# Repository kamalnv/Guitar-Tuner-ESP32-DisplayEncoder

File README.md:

# ESP32 Guitar Tuner

A full-featured guitar tuner running on ESP32 with OLED display and rotary encoder for standard 6 string Guitar, 
has a Audio module for a mic, 

if you are looking for bass Guitar, 7 string guitar or as a Pedal you can try the V2 Branch

This code is by Emergent.sh use it at your descrete & risks.

## Hardware Requirements

### Components
1. **ESP32 DevKit** (or any generic ESP32 board)
2. **0.96" OLED Display Module with EC11 Rotary Encoder** 
   - Display: SSD1306, 128x32 pixels, I2C interface
   - Rotary Encoder: EC11 with push button
   - [Product Link](https://robu.in/product/0-96-inch-oled-display-screen-rotary-encoder/)
3. **Electret Microphone Module** (MAX9814 or MAX4466 recommended)

### Wiring Diagram

```
ESP32          OLED+Encoder Module (9-pin header)
------         ---------------------------------
3.3V    -----> VCC
GND     -----> GND
GPIO21  -----> SDA (I2C Data)
GPIO22  -----> SCL (I2C Clock)
GPIO32  -----> CLK (Encoder A)
GPIO33  -----> DT  (Encoder B)
GPIO25  -----> SW  (Encoder Button)

ESP32          Microphone Module
------         -----------------
3.3V    -----> VCC
GND     -----> GND
GPIO34  -----> OUT (Analog output)
```

### Pin Summary
| Function | ESP32 Pin |
|----------|-----------|
| I2C SDA  | GPIO 21   |
| I2C SCL  | GPIO 22   |
| Encoder CLK | GPIO 32 |
| Encoder DT  | GPIO 33 |
| Encoder SW  | GPIO 25 |
| Mic OUT  | GPIO 34   |

## Software Setup

### Arduino IDE Setup

1. **Install ESP32 Board Support**
   - Open Arduino IDE
   - Go to `File > Preferences`
   - Add to "Additional Board Manager URLs":
     ```
     https://raw.githubusercontent.com/espressif/arduino-esp32/gh-pages/package_esp32_index.json
     ```
   - Go to `Tools > Board > Boards Manager`
   - Search "ESP32" and install "esp32 by Espressif Systems"

2. **Install Required Libraries**
   - Go to `Sketch > Include Library > Manage Libraries`
   - Install:
     - `Adafruit GFX Library`
     - `Adafruit SSD1306`

3. **Select Board**
   - Go to `Tools > Board > ESP32 Arduino`
   - Select "ESP32 Dev Module" or your specific board

4. **Upload Settings**
   - Upload Speed: 921600
   - CPU Frequency: 240MHz
   - Flash Frequency: 80MHz
   - Flash Mode: QIO
   - Flash Size: 4MB
   - Partition Scheme: Default 4MB with spiffs

5. **Upload**
   - Connect ESP32 via USB
   - Select correct COM port in `Tools > Port`
   - Click Upload

## Usage

### Menu Navigation
- **Rotate encoder**: Switch between tuning modes
- **Push encoder**: Enter/exit tuning mode

### Tuning Modes

| Mode | Description | Strings |
|------|-------------|---------|
| **CHROMATIC** | All 12 notes | Any note |
| **STANDARD** | Standard guitar | E A D G B E |
| **DROP D** | Drop D guitar | D A D G B E |
| **HALF DOWN** | Half step down | Eb Ab Db Gb Bb Eb |
| **DROP C** | Drop C guitar | C G C F A D |
| **OPEN G** | Open G guitar | D G D G B D |
| **DADGAD** | Celtic tuning | D A D G A D |
| **7-STRING** | 7-string standard | B E A D G B E |
| **7STR DROP A** | 7-string Drop A | A E A D G B E |
| **BASS 4-STR** | 4-string bass | E A D G |
| **BASS 5-STR** | 5-string bass | B E A D G |
| **BASS DROP D** | Bass Drop D | D A D G |

### Display Information

#### Chromatic Mode
```
┌──────────────────────────┐
│ E4  329.6Hz         OK   │
│     +2.5c                │
│ ◄═══════════╪═══════════►│
└──────────────────────────┘
```
- Note name and octave
- Detected frequency
- Cents deviation (+/- from target)
- Visual tuning meter

#### Guitar Mode
```
┌──────────────────────────┐
│ STR 6: E2    82.4Hz      │
│ +3.2 cents     TUNE DN   │
│ ◄═══════════╪═══════════►│
└──────────────────────────┘
```
- String number and target note
- Detected frequency
- Cents deviation
- Tuning direction indicator
- Visual tuning meter

### Tuning Tips

1. **In Tune**: Meter indicator in center, "OK" or "IN TUNE!" displayed
2. **Tune Up**: Note is flat (low), increase string tension
3. **Tune Down**: Note is sharp (high), decrease string tension
4. **Target**: Keep cents deviation within ±5 cents

## Troubleshooting

### No Display
- Check I2C connections (SDA, SCL)
- Verify OLED address is 0x3C (can try 0x3D)
- Check power supply (3.3V)

### Encoder Not Responding
- Verify CLK, DT, SW connections
- Check for loose connections
- Ensure pull-up resistors are enabled (internal pull-ups used)

### No Pitch Detection
- Check microphone connections
- Ensure microphone gain is adequate
- Play note closer to microphone
- Check for environmental noise

### Inaccurate Readings
- Allow mic to warm up
- Play notes clearly and sustain
- Avoid background noise
- Ensure good power supply

## Technical Details

### Pitch Detection Algorithm
- Uses **autocorrelation** for fundamental frequency detection
- Sample rate: 8000 Hz
- Buffer size: 1024 samples
- Frequency range: 60 Hz - 1200 Hz (covers all guitar strings)

### Display
- Resolution: 128 x 32 pixels
- Driver: SSD1306
- Interface: I2C @ 400kHz

### Accuracy
- Typical accuracy: ±1-2 cents under good conditions
- Refresh rate: ~10 Hz

## License

Open source - free to use and modify.

## Credits

Built for the ESP32 platform using:
- Adafruit GFX Library
- Adafruit SSD1306 Library
- ESP32 Arduino Core

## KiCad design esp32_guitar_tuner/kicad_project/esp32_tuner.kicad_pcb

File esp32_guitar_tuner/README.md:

# ESP32 Guitar Tuner

A full-featured guitar tuner running on ESP32 with OLED display and rotary encoder.

## Hardware Requirements

### Components
1. **ESP32 DevKit** (or any generic ESP32 board)
2. **0.96" OLED Display Module with EC11 Rotary Encoder** 
   - Display: SSD1306, 128x32 pixels, I2C interface
   - Rotary Encoder: EC11 with push button
   - [Product Link](https://robu.in/product/0-96-inch-oled-display-screen-rotary-encoder/)
3. **Direct Guitar Input Circuit** (see below)

### Guitar Input Preamp Components
| Qty | Component | Value | Notes |
|-----|-----------|-------|-------|
| 1 | TL072 or LM358 | - | Dual op-amp IC |
| 1 | 1/4" Mono Audio Jack | - | Guitar input |
| 1 | Resistor | 1MΩ | Input impedance |
| 2 | Resistor | 100kΩ | Bias divider + feedback |
| 1 | Resistor | 10kΩ | Feedback |
| 1 | Resistor | 47kΩ | Output protection |
| 2 | Electrolytic Capacitor | 10µF | Coupling caps |
| 1 | Ceramic Capacitor | 100nF | Power decoupling |

### Wiring Diagram

```
ESP32          OLED+Encoder Module (9-pin header)
------         ---------------------------------
3.3V    -----> VCC
GND     -----> GND
GPIO21  -----> SDA (I2C Data)
GPIO22  -----> SCL (I2C Clock)
GPIO32  -----> CLK (Encoder A)
GPIO33  -----> DT  (Encoder B)
GPIO25  -----> SW  (Encoder Button)

ESP32          Guitar Preamp Circuit Output
------         ----------------------------
3.3V    -----> Op-amp VCC (pin 8)
GND     -----> Op-amp GND (pin 4)
GPIO34  -----> Preamp output (via 47kΩ)
```

### Guitar Input Preamp Schematic
```
                      +3.3V
                        │
                   ┌────┴────┐
                   │  100kΩ  │
                   └────┬────┘
                        │ (1.65V bias)
                   ┌────┴────┐
                   │  100kΩ  │
                   └────┬────┘
                        │
                       GND

  GUITAR    1MΩ     10µF    ┌─────────────┐
  TIP ────[====]───┤├──●────┤ 3   TL072  1├────┤├────[47kΩ]───> GPIO34
                        │    │      A      │   10µF
                   (bias)────┤ 2          8├────(+3.3V)
                             │             │
                         ┌───┤            4├────(GND)
                         │   └─────────────┘
                       10kΩ        │
                         │       100kΩ
                        GND        │
                                   └──────────────┘
                                   (feedback loop)

  GUITAR
  SLEEVE ──────────────────────────────────────────> GND
```

See `GUITAR_INPUT_CIRCUIT.h` for detailed schematic and breadboard layout.

### Pin Summary
| Function | ESP32 Pin |
|----------|-----------|
| I2C SDA  | GPIO 21   |
| I2C SCL  | GPIO 22   |
| Encoder CLK | GPIO 32 |
| Encoder DT  | GPIO 33 |
| Encoder SW  | GPIO 25 |
| Guitar IN | GPIO 34  |

## Software Setup

### Arduino IDE Setup

1. **Install ESP32 Board Support**
   - Open Arduino IDE
   - Go to `File > Preferences`
   - Add to "Additional Board Manager URLs":
     ```
     https://raw.githubusercontent.com/espressif/arduino-esp32/gh-pages/package_esp32_index.json
     ```
   - Go to `Tools > Board > Boards Manager`
   - Search "ESP32" and install "esp32 by Espressif Systems"

2. **Install Required Libraries**
   - Go to `Sketch > Include Library > Manage Libraries`
   - Install:
     - `Adafruit GFX Library`
     - `Adafruit SSD1306`

3. **Select Board**
   - Go to `Tools > Board > ESP32 Arduino`
   - Select "ESP32 Dev Module" or your specific board

4. **Upload Settings**
   - Upload Speed: 921600
   - CPU Frequency: 240MHz
   - Flash Frequency: 80MHz
   - Flash Mode: QIO
   - Flash Size: 4MB
   - Partition Scheme: Default 4MB with spiffs

5. **Upload**
   - Connect ESP32 via USB
   - Select correct COM port in `Tools > Port`
   - Click Upload

## Usage

### Menu Navigation
- **Rotate encoder**: Switch between tuning modes
- **Push encoder**: Enter/exit tuning mode

### Tuning Modes

| Mode | Description | Strings |
|------|-------------|---------|
| **CHROMATIC** | All 12 notes | Any note |
| **STANDARD** | Standard guitar | E A D G B E |
| **DROP D** | Drop D guitar | D A D G B E |
| **HALF DOWN** | Half step down | Eb Ab Db Gb Bb Eb |
| **DROP C** | Drop C guitar | C G C F A D |
| **OPEN G** | Open G guitar | D G D G B D |
| **DADGAD** | Celtic tuning | D A D G A D |
| **7-STRING** | 7-string standard | B E A D G B E |
| **7STR DROP A** | 7-string Drop A | A E A D G B E |
| **BASS 4-STR** | 4-string bass | E A D G |
| **BASS 5-STR** | 5-string bass | B E A D G |
| **BASS DROP D** | Bass Drop D | D A D G |

### Display Information

#### Chromatic Mode
```
┌──────────────────────────┐
│ E4  329.6Hz         OK   │
│     +2.5c                │
│ ◄═══════════╪═══════════►│
└──────────────────────────┘
```
- Note name and octave
- Detected frequency
- Cents deviation (+/- from target)
- Visual tuning meter

#### Guitar Mode
```
┌──────────────────────────┐
│ STR 6: E2    82.4Hz      │
│ +3.2 cents     TUNE DN   │
│ ◄═══════════╪═══════════►│
└──────────────────────────┘
```
- String number and target note
- Detected frequency
- Cents deviation
- Tuning direction indicator
- Visual tuning meter

### Tuning Tips

1. **In Tune**: Meter indicator in center, "OK" or "IN TUNE!" displayed
2. **Tune Up**: Note is flat (low), increase string tension
3. **Tune Down**: Note is sharp (high), decrease string tension
4. **Target**: Keep cents deviation within ±5 cents

## Troubleshooting

### No Display
- Check I2C connections (SDA, SCL)
- Verify OLED address is 0x3C (can try 0x3D)
- Check power supply (3.3V)

### Encoder Not Responding
- Verify CLK, DT, SW connections
- Check for loose connections
- Ensure pull-up resistors are enabled (internal pull-ups used)

### No Pitch Detection
- Check guitar cable connection
- Verify preamp circuit is powered (3.3V to op-amp)
- Check 10µF capacitors are correct polarity
- Ensure op-amp output reaches GPIO34
- Try a different guitar/cable

### Inaccurate Readings
- Adjust preamp gain if signal clips (reduce 100kΩ feedback resistor)
- Check for loose connections in preamp circuit
- Ensure good solder joints
- Use shielded cable from preamp to ESP32

### Signal Too Weak
- Increase gain: use 220kΩ instead of 100kΩ for feedback
- Check guitar volume knob is up
- Verify 1MΩ input resistor value

### Signal Clipping (Distorted)
- Decrease gain: use 47kΩ instead of 100kΩ for feedback
- For hot humbuckers, gain of 5-6 may be sufficient

## Technical Details

### Pitch Detection Algorithm
- Uses **autocorrelation** for fundamental frequency detection
- Sample rate: 8000 Hz
- Buffer size: 1024 samples
- Frequency range: 60 Hz - 1200 Hz (covers all guitar strings)

### Display
- Resolution: 128 x 32 pixels
- Driver: SSD1306
- Interface: I2C @ 400kHz

### Accuracy
- Typical accuracy: ±1-2 cents under good conditions
- Refresh rate: ~10 Hz

## License

Open source - free to use and modify.

## Credits

Built for the ESP32 platform using:
- Adafruit GFX Library
- Adafruit SSD1306 Library
- ESP32 Arduino Core

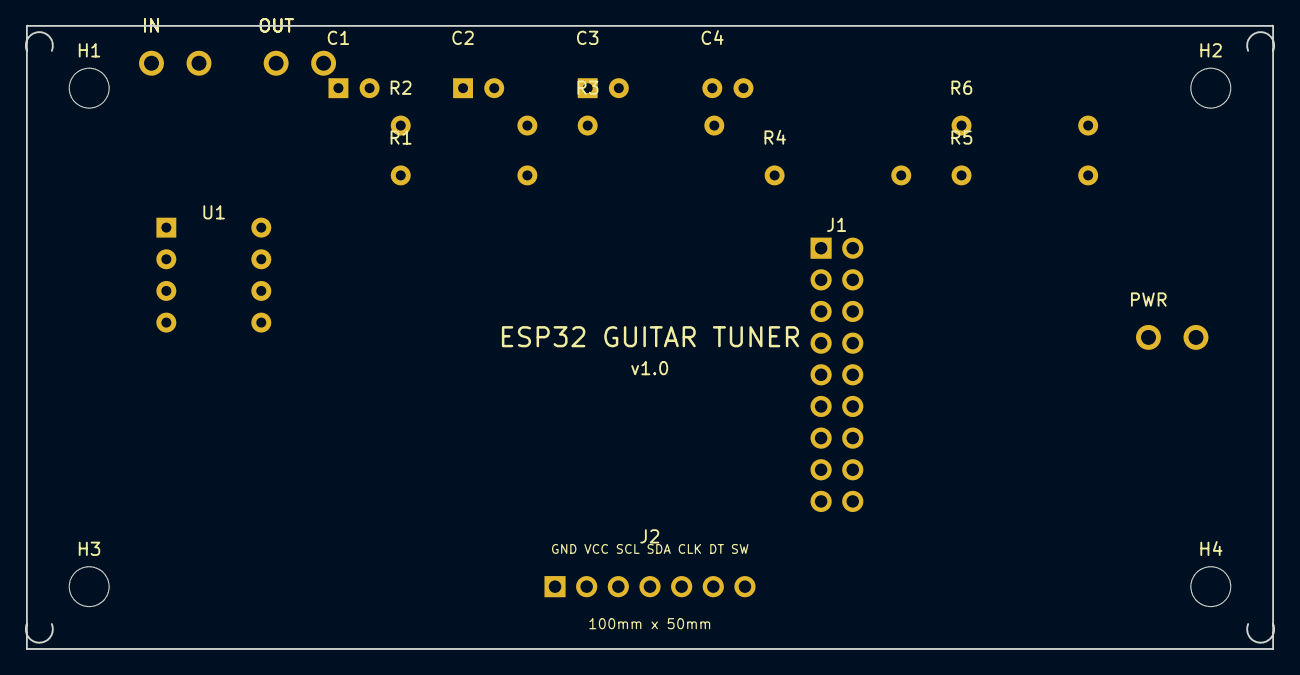
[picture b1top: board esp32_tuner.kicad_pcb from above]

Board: 2 copper layers, 100.2 x 50.0 mm, 20 parts (0 on the bottom side), 11 nets, no tracks yet.

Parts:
C1, C2, C3: 10uF; CP_Radial_D5.0mm_P2.50mm
C4: 100nF; C_Disc_D5.0mm_W2.5mm_P2.50mm
H1, H2, H3, H4: MountingHole_3.2mm_M3
IN: INPUT; SolderWirePad_1x02_P3.81mm_D1.0mm
J1: ESP-WROOM-32; PinHeader_2x09_P2.54mm_Vertical
J2: OLED_ENC; PinHeader_1x07_P2.54mm_Vertical
OUT: OUTPUT; SolderWirePad_1x02_P3.81mm_D1.0mm
PWR: 5V_IN; SolderWirePad_1x02_P3.81mm_D1.0mm
R1: 1M; R_Axial_DIN0207_L6.3mm_D2.5mm_P10.16mm_Horizontal
R2, R3, R5: 100k; R_Axial_DIN0207_L6.3mm_D2.5mm_P10.16mm_Horizontal
R4: 10k; R_Axial_DIN0207_L6.3mm_D2.5mm_P10.16mm_Horizontal
R6: 47k; R_Axial_DIN0207_L6.3mm_D2.5mm_P10.16mm_Horizontal
U1: TL072; DIP-8_W7.62mm

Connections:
+3V3: C4.1, J1.1, J2.2, R2.1, U1.8
AUDIO_IN: IN.1, R1.1
GND: C4.2, IN.2, J1.2, J1.18, J2.1, OUT.2, PWR.2, R3.2, R4.2, U1.4
GPIO21: J1.13, J2.4
GPIO22: J1.14, J2.3
GPIO25: J1.5, J2.7
GPIO32: J1.7, J2.5
GPIO33: J1.8, J2.6
GPIO34: J1.9, R6.2
OPAMP_OUT_A: C3.1, R5.2, U1.1
VREF: R2.2, R3.1, U1.3

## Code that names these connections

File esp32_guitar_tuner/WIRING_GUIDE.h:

/*
 * ESP32 Guitar Tuner - Wiring Guide
 * ==================================
 * 
 * ASCII Wiring Diagram:
 * 
 *                    ┌─────────────────────────────┐
 *                    │    OLED + ENCODER MODULE    │
 *                    │    (9-Pin Header)           │
 *                    │                             │
 *                    │  ┌───────────────────────┐  │
 *                    │  │   0.96" OLED Display  │  │
 *                    │  │      (SSD1306)        │  │
 *                    │  │      128 x 32         │  │
 *                    │  └───────────────────────┘  │
 *                    │                             │
 *                    │     ┌───┐                   │
 *                    │     │ ◯ │  EC11 Rotary     │
 *                    │     │   │  Encoder         │
 *                    │     └───┘  (with button)   │
 *                    │                             │
 *                    │  [VCC][GND][SCL][SDA]       │
 *                    │  [CLK][DT][SW][NC][NC]      │
 *                    └──┬───┬───┬───┬───┬───┬─────┘
 *                       │   │   │   │   │   │
 *     ┌─────────────────┼───┼───┼───┼───┼───┼──────────────────┐
 *     │                 │   │   │   │   │   │                  │
 *     │    ┌────────────┼───┼───┼───┼───┼───┼────────────┐     │
 *     │    │            │   │   │   │   │   │            │     │
 *     │    │   3.3V ────┘   │   │   │   │   │            │     │
 *     │    │   GND ─────────┘   │   │   │   │            │     │
 *     │    │   GPIO22 ──────────┘   │   │   │  SCL       │     │
 *     │    │   GPIO21 ──────────────┘   │   │  SDA       │     │
 *     │    │   GPIO32 ──────────────────┘   │  CLK       │     │
 *     │    │   GPIO33 ──────────────────────┘  DT        │     │
 *     │    │   GPIO25 ──────────────────────── SW        │     │
 *     │    │                                             │     │
 *     │    │               ESP32                         │     │
 *     │    │            DevKit Board                     │     │
 *     │    │                                             │     │
 *     │    │   GPIO34 ─────────────────┐  (ADC Input)    │     │
 *     │    │   3.3V ──────────────┐    │                 │     │
 *     │    │   GND ──────────┐    │    │                 │     │
 *     │    │                 │    │    │                 │     │
 *     │    └─────────────────┼────┼────┼─────────────────┘     │
 *     │                      │    │    │                       │
 *     │                      │    │    │                       │
 *     │                 ┌────┼────┼────┼────┐                  │
 *     │                 │    │    │    │    │                  │
 *     │                 │  [GND][VCC][OUT]  │                  │
 *     │                 │                   │                  │
 *     │                 │  ELECTRET MIC     │                  │
 *     │                 │  MODULE           │                  │
 *     │                 │  (MAX9814/4466)   │                  │
 *     │                 │       🎤          │                  │
 *     │                 └───────────────────┘                  │
 *     │                                                        │
 *     └────────────────────────────────────────────────────────┘
 * 
 * 
 * CONNECTION TABLE:
 * ================
 * 
 * ┌─────────────────┬─────────────┬─────────────────────────────┐
 * │ OLED+Encoder    │ ESP32 Pin   │ Notes                       │
 * ├─────────────────┼─────────────┼─────────────────────────────┤
 * │ VCC             │ 3.3V        │ Power supply                │
 * │ GND             │ GND         │ Ground                      │
 * │ SCL             │ GPIO 22     │ I2C Clock                   │
 * │ SDA             │ GPIO 21     │ I2C Data                    │
 * │ CLK             │ GPIO 32     │ Encoder rotation (A)        │
 * │ DT              │ GPIO 33     │ Encoder rotation (B)        │
 * │ SW              │ GPIO 25     │ Encoder push button         │
 * └─────────────────┴─────────────┴─────────────────────────────┘
 * 
 * ┌─────────────────┬─────────────┬─────────────────────────────┐
 * │ Guitar Preamp   │ ESP32 Pin   │ Notes                       │
 * ├─────────────────┼─────────────┼─────────────────────────────┤
 * │ Preamp OUT      │ GPIO 34     │ Via 47kΩ protection resistor│
 * │ Op-amp VCC      │ 3.3V        │ TL072/LM358 pin 8           │
 * │ Op-amp GND      │ GND         │ TL072/LM358 pin 4           │
 * └─────────────────┴─────────────┴─────────────────────────────┘
 * 
 * See GUITAR_INPUT_CIRCUIT.h for complete preamp schematic!
 * 
 * 
 * IMPORTANT NOTES:
 * ===============
 * 
 * 1. GPIO 34 is INPUT ONLY (no internal pull-up), perfect for ADC
 * 
 * 2. Use GPIO 32, 33, 25 for encoder because they support interrupts
 * 
 * 3. I2C default address for SSD1306 is usually 0x3C
 *    If display doesn't work, try 0x3D
 * 
 * 4. For best audio quality with direct guitar input:
 *    - Use TL072 (better audio) or LM358 (cheaper)
 *    - Keep wires short between preamp and ESP32
 *    - Use shielded cable if possible
 *    - Position preamp close to ESP32
 * 
 * 5. The OLED+Encoder module's 9-pin header typically has:
 *    Pin 1: VCC
 *    Pin 2: GND  
 *    Pin 3: SCL
 *    Pin 4: SDA
 *    Pin 5: CLK (Encoder A)
 *    Pin 6: DT (Encoder B)
 *    Pin 7: SW (Button)
 *    Pin 8-9: NC (Not Connected) or additional functions
 *    
 *    CHECK YOUR MODULE'S ACTUAL PINOUT - it may vary!
 * 
 * 
 * GUITAR INPUT OPTIONS:
 * =====================
 * 
 * OPTION 1: Active Preamp (Recommended)
 *    - Uses TL072 or LM358 op-amp
 *    - Best signal quality
 *    - Works with all pickup types
 *    - See GUITAR_INPUT_CIRCUIT.h for schematic
 * 
 * OPTION 2: Passive Input (Simpler, Lower Quality)
 *    - No amplification, just bias
 *    - Works best with hot pickups (humbuckers)
 *    - May struggle with single coils
 * 
 *    GUITAR ──[10µF]──┬──[100kΩ]──(+3.3V)
 *    TIP              │
 *                     ├──[100kΩ]──(GND)
 *                     │
 *                     └──[47kΩ]──> GPIO34
 *    SLEEVE ─────────────────────> GND
 * 
 */

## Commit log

2026-03-05 auto-commit for 0b4ddda7-aa90-4dfe-84d9-176dfbac5809
2026-03-05 Auto-generated changes
2026-03-05 auto-commit for 0f8fd846-c83f-4faf-8839-9a6468260c06
2026-03-05 auto-commit for 1e49d061-dc98-4fd8-8929-e045f9f37f9a
2026-03-05 auto-commit for 6728f17c-dea5-41ea-a244-87b7c5cc899a
2026-03-05 Include usage disclaimer in README
    Added a disclaimer about code usage risks.
2026-03-05 Enhance README with additional project details
    Expanded project description to include details about guitar types and audio module.
2026-03-05 Clarify compatibility for bass and 7 string guitars
    Updated README to clarify compatibility with bass and 7 string guitars.
2026-03-05 auto-commit for 3f7c8f3b-bd3f-495f-b374-19cf78f4d433
2026-03-05 auto-commit for bfbed46f-319d-4bb3-ba51-381d17b902d6
2026-03-05 auto-commit for f085cd03-9003-41cf-b78d-f5f4ca8e5b0b
2026-03-05 auto-commit for d1a616c5-6545-4b01-95df-629938f1d575
2026-03-05 auto-commit for 4a40b917-fded-4080-9e50-19c0e38c70d6
